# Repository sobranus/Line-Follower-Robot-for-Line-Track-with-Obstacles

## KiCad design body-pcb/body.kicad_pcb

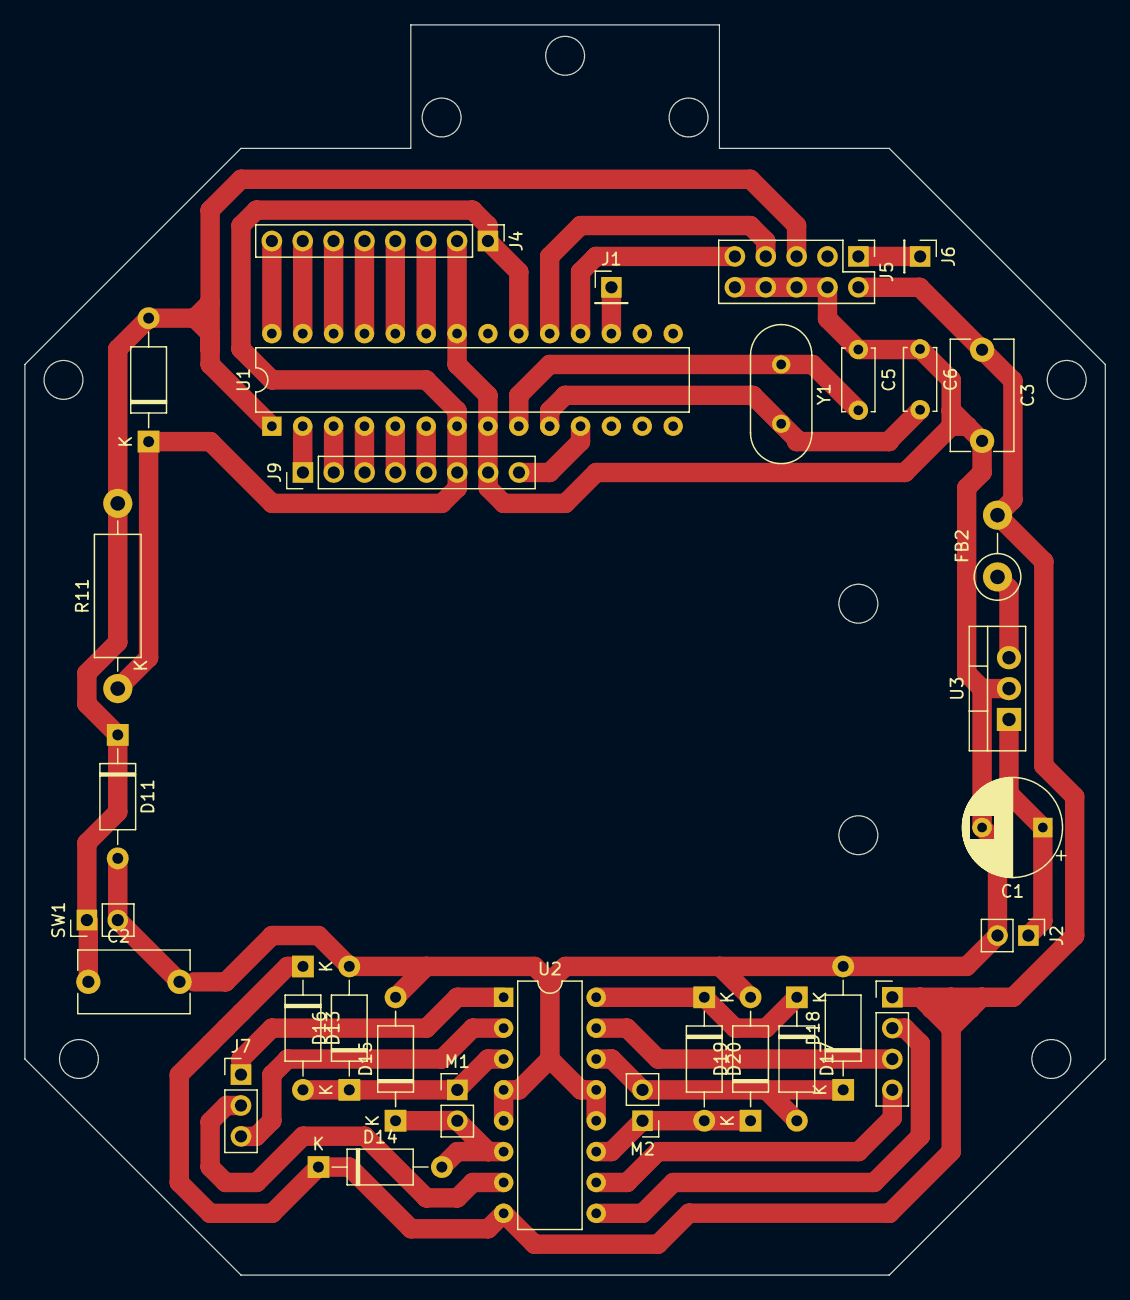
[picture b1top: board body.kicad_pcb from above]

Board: 2 copper layers, 88.9 x 102.9 mm, 32 parts (0 on the bottom side), 33 nets.

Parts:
C1: 470uF; CP_Radial_D8.0mm_P5.00mm
C2, C3: 100nF; C_Disc_D9.0mm_W5.0mm_P7.50mm
C5, C6: 22pF; C_Disc_D5.0mm_W2.5mm_P5.00mm
D8, D11, D13, D14, D15, D16, D17, D18, D19, D20: D; D_A-405_P10.16mm_Horizontal
FB2: FerriteBead; R_Axial_DIN0411_L9.9mm_D3.6mm_P5.08mm_Vertical
J1, J6: Conn_01x01_Socket; PinHeader_1x01_P2.54mm_Vertical
J2: Conn_01x02_Socket; PinHeader_1x02_P2.54mm_Vertical
J4, J9: Conn_01x08_Socket; PinHeader_1x08_P2.54mm_Vertical
J5: Conn_02x05_Odd_Even; PinHeader_2x05_P2.54mm_Vertical
J7: Conn_01x03_Socket; PinHeader_1x03_P2.54mm_Vertical
J8: Conn_01x04_Socket; PinHeader_1x04_P2.54mm_Vertical
M1, M2: Motor_DC; PinHeader_1x02_P2.54mm_Vertical
R11: 4.7k; R_Axial_DIN0411_L9.9mm_D3.6mm_P15.24mm_Horizontal
SW1: SW_Push; PinHeader_1x02_P2.54mm_Vertical
U1: ATmega328-P; DIP-28_W7.62mm
U2: L293D; DIP-16_W7.62mm
U3: L7805; TO-220-3_Vertical
Y1: Crystal; Crystal_HC49-4H_Vertical

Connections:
GND: C1.2, C2.2, C3.2, C5.1, C6.1, D11.2 (A), D15.2 (A), D16.2 (A), D18.2 (A), D19.2 (A), J2.2, J4.2, J5.4, J5.6, J5.8, J5.10, J9.7, SW1.2, U1.8 (GND), U1.22 (GND), U2.4 (GND), U2.5 (GND), U2.12 (GND), U2.13 (GND), U3.2 (GND)
unnamed: C2.1, D8.2 (A), D11.1 (K), J5.5, R11.2, SW1.1, U1.1 (~RESET/PC6)
unnamed: D13.2 (A), D16.1 (K), M1.1 (+), U2.3 (1Y)
unnamed: D14.2 (A), D15.1 (K), M1.2 (-), U2.6 (2Y)
unnamed: D17.2 (A), D18.1 (K), M2.2 (-), U2.14 (4Y)
unnamed: D19.1 (K), D20.2 (A), M2.1 (+), U2.11 (3Y)
unnamed: J1.1, U1.17 (PB3)
unnamed: C1.1, J2.1, U3.1 (IN)
unnamed: J4.3, U1.23 (PC0)
unnamed: J4.4, U1.24 (PC1)
unnamed: J4.5, U1.25 (PC2)
unnamed: J4.6, U1.26 (PC3)
unnamed: J4.7, U1.27 (PC4)
unnamed: J4.8, U1.28 (PC5)
unnamed: J5.1, J6.1
unnamed: J5.7, U1.19 (PB5)
unnamed: J5.9, U1.18 (PB4)
unnamed: J7.1, U2.1 (EN1,2)
unnamed: J7.2, U2.7 (2A)
unnamed: J7.3, U2.2 (1A)
unnamed: J8.2, U2.9 (EN3,4)
unnamed: J8.3, U2.15 (4A)
unnamed: J8.4, U2.10 (3A)
unnamed: J9.1, U1.2 (PD0)
unnamed: J9.2, U1.3 (PD1)
unnamed: J9.3, U1.4 (PD2)
unnamed: J9.4, U1.5 (PD3)
unnamed: J9.5, U1.6 (PD4)
unnamed: J9.8, U1.11 (PD5)
unnamed: C5.2, U1.9 (XTAL1/PB6), Y1.1
unnamed: C6.2, U1.10 (XTAL2/PB7), Y1.2
unnamed: FB2.1, U3.3 (OUT)
VCC: C3.1, D8.1 (K), D13.1 (K), D14.1 (K), D17.1 (K), D20.1 (K), FB2.2, J4.1, J5.2, J8.1, J9.6, R11.1, U1.7 (VCC), U1.20 (AVCC), U2.8 (VCC2), U2.16 (VCC1)

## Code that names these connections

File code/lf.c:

#include <avr/io.h>
#incude <util/delay.h>

uint16_t result[6];

void init_output(void) {
	DDRD |= _BV(PD0) | _BV(PD1) | _BV(PD2) | _BV(PD3) | _BV(PD4) | _BV(PD5);
}

void init_adc(void) {
	ADMUX = (1 << REFS0);
	ADCSRA = (1 << ADPS2) | (1 << ADPS1) | (1 << ADPS0);
	ADCSRA |= (1 << ADEN);
}

uint16_t adc_read(uint8_t adc_channel) {
	ADMUX = (ADMUX & 0xF8) | (adc_channel & 0x07);
	ADCSRA |= (1 <<ADSC);
	
	while (ADCSRA & (1 << ADSC)) {
	
	return ADC;
}

int main(void) {
	init_output();
	init_adc();
	
	PORTD |= _BV(PD2);
	PORTD &= ~_BV(PD1);
	PORTD |= _BV(PD4);
	PORTD &= ~_BV(PD3);
	
	while (1) {
		for (int i = 0; i < 6; i++) {
			result[i] = adc_read(i);
		}
		
		if (result[1] >= 300 || result[0] >= 300) {
			PORTD |= _BV(PD5);
			PORTD &= ~_BV(PD0);
		} else if (result[4] >= 400 || result[5] >= 800) {
			PORTD |= _BV(PD0);
			PORTD &= ~_BV(PD5);
		}
			
		} else {
			PORTD |= _BV(PD0);
			PORTD |= _BV(PD5);
		}
		_delay_ms(100);
	}
	return 0;
}
